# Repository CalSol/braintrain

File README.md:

# braintrain
These are a series of introductory self-paced labs teaching beginning embedded software engineering concepts.

Labs currently available:
- [Lab 1: Embedded Introduction](lab1.md)
- [Lab 2: CAN Bus and Multitasking](lab2.md)

References for non-firmware labs:
- [Soldering](soldering.md)

Coming soon:
- Suggest something!

## Setup
To get started, you need to setup the PlatformIO build system and clone this repository.
Follow the [detailed setup instructions](SETUP.md).

## Troubleshooting
Find the solutions to your troubles here:
- [Troubleshoot.md](Troubleshoot.md)
- [CalSol Wiki on Nucleo](https://www.google.com/) Sorry I forgot the link. You can search it up on the wiki.

## Quick Reference
To upload firmware to the board from the command line, run:
```
pio run -t upload
```

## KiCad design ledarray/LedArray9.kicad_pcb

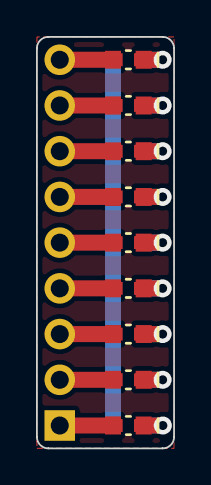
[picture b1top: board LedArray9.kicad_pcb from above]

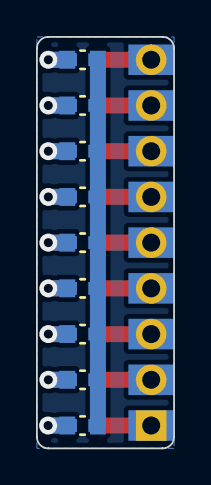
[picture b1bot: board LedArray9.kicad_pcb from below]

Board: 2 copper layers, 7.6 x 22.9 mm, 19 parts (10 on the bottom side), 19 nets.

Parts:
D1, D2, D3, D4, D5, D6, D7, D8, D9: D; LED_0603_0402_combo
J1: Conn_01x09; Pin_Header_Inline_1x09_Pitch2.54mm
R1, R2, R3, R4, R5, R6, R7, R8, R9: R; R_0603_0402_combo

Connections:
unnamed: D1.1, R1.2
unnamed: D1.2, J1.1
unnamed: D2.1, R2.2
unnamed: D2.2, J1.2
unnamed: D3.1, R3.2
unnamed: D3.2, J1.3
unnamed: D4.1, R4.2
unnamed: D4.2, J1.4
unnamed: D5.1, R5.2
unnamed: D5.2, J1.5
unnamed: D6.1, R6.2
unnamed: D6.2, J1.6
unnamed: D7.1, R7.2
unnamed: D7.2, J1.7
unnamed: D8.1, R8.2
unnamed: D8.2, J1.8
unnamed: D9.1, R9.2
unnamed: D9.2, J1.9
unnamed: R1.1, R2.1, R3.1, R4.1, R5.1, R6.1, R7.1, R8.1, R9.1

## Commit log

2016-11-30 Add submodules
2016-11-30 Import zephyr libraries, initial main
2016-12-23 Refactors to use latest mbed, remove zephyr-common pending further refactoring
2016-12-25 Reduce clock rate to 12MHz using override system files, up default baud to 115200
2016-12-26 Clean skeleton code with broken out utils
2016-12-26 Use stdlib abs and fabs, which result in faster runtime
2016-12-26 Default to -O2 optimization
2016-12-28 First two labs
2016-12-28 Lab 1.4 and updates to previous
2016-12-28 fixes
2016-12-28 fix cross-repo links
2016-12-29 Finish lab 1
2016-12-29 try reformatting
2016-12-29 Remove unused code, corrections to lab
2016-12-29 Add braintest binaries and source
2016-12-29 braintest instructions
2016-12-30 diagrams and DONE
2016-12-31 Add debouncing mention
2017-01-05 Auto-build solutions, add openocd build target
2017-01-30 Use upstream mbed
2017-02-21 can intro
2017-02-21 CAN PHY overview
2017-02-21 unreverse links
2017-02-21 lab sketch
2017-02-21 rewording
2017-02-22 Lab 2.2 and partial master node code
2017-02-27 Lab2 master debouncing code
2017-03-06 Updated lab2 master with RGB LED and CAN spam
2017-03-06 refactor RGB LED
2017-03-06 fix RGB LED code
2017-03-06 Rest of lab2
2017-03-06 cooperative multitasking
2017-03-06 add rtos to build
2017-03-08 RTOS lab 2.6
2017-03-08 RTOS lab
2017-03-09 rewrite threading discussion
2017-03-10 Build the USBDevice library
2017-03-10 Add SLCAN debug interface
    Add quasi-standard CAN-USB/SLCAN protocol CAN debug support
    See lab2slcan for example usage
2017-03-10 Change lab2slcan to use native USB
2017-03-10 Add BufferedRXSerial class
    Add interrupt-based buffered RX serial class
    Add utility library to the build (for solutions only)
2017-03-10 Add USBSLCANSlave for SLCAN over native USB
    Refactor command buffering into SLCANBase::readCommand()
    Split SerialSLCAN details into its own header and implementation file
    Add USBSLCAN implementation
2017-03-10 Move lab2slcan to util/
2017-03-11 Silently ignore empty commands
2017-03-11 Fix responses to diagnostic commands over USB
2017-03-11 Remove the hardware serial SLCAN implementation
    Removed the SerialSLCANBase/SerialSLCANMaster/Slave classes
    Removed BufferedSerial, as it no longer has a purpose
    Changed SLCANBase::readCommand() to use wrapper methods in subclasses
    instead of directly calling stream.readable() and stream.getc() to avoid
    interface splitting issues
2017-03-11 Only echo CAN messages sent by the node, not the host
2017-03-11 Fix hang when disconnecting USB
    Add NonBlockingUSBSerial class to expose the nonblocking USB EP write
    API via writeBlockNB
    Change the activity flag to only be used for reporting activity.
    Always attempt to flush the SLCAN USB output buffer to avoid stalling on
    a full packet buffer
2017-03-11 Reset output buffers after a USB disconnect
2017-03-11 fixup! Fix hang when disconnecting USB
2017-03-11 Change command responses to return fixed lengths
    execCommand no longer nul-terminates response strings - the result is
    either the length returned by commandResponseLength() on success or 1 on
    failure
    Pass the command response directly into the output packet buffer
2017-03-11 Move USBDevice build into SConscript-env-lpc1549
2017-03-12 Add CAN->USB debugging using the SLCAN protocol
    This commit adds a lab2slcan variant of the lab2master node firmware that reports CAN messages over USB using the CAN-USB/SLCAN[1] protocol.
    The lab2slcan firmware and supporting files can be found under the util/ directory.
    Some CAN-USB commands have not been fully implemented. For compatibility, several commands are accepted, but have no effect. In particular, the lab2slcan firmware will not allow the host PC to change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
    The lab2slcan firmware has been tested for compatibility with USBtinViewer[2] and the UAVCAN GUI Tool[3].
    1: http://www.can232.c
2017-03-12 fix some code, use non-RTR frames
2017-03-12 Lab 2 updates
2017-03-12 Master SLCAN transmit loopback
2017-03-12 caveat
2017-03-12 better index
2017-03-13 add voltage instruction
2017-03-24 Add notes on zephyr-common stuff
2018-09-18 Fix gitmodules to use HTTPS
2018-10-05 Update build system with Tachyon-FW system
2018-10-05 refactor out libs to be more independent of mbed
2018-10-05 improved docs
2018-10-05 no more zephyr races
2018-10-05 remove some legacy stuff
2018-10-16 Update build system and readme (#4)
    Update build system with Tachyon-FW system
2019-02-15 rami doing the brain training and practicing git; do not use
2019-09-07 Adding Mac serial instructions, need pics
2019-09-08 my old braintrain solution
2019-09-08 2019 CAN Controller Blinky, change pin outs for each brain
2019-09-09 minor changes to lab text
2019-09-15 Clarify parts of the RGB led section
2019-09-15 Header instructions
2019-09-19 Added brain pinout diagram
2019-10-21 Clarify how to clone
2019-10-21 Lab 5
2020-03-05 Adding last changes to main
2020-10-12 add stm32f303k8 build support alongside lpc1549
2020-10-12 revert brain dirs for doc compatibility
2020-10-13 Fix RTOS platform target
2020-10-13 add hue blinky for stm32
2020-10-19 Nucleo F303K8 build (#6)
    * add stm32f303k8 build support alongside lpc1549
    * revert brain dirs for doc compatibility
    * Fix RTOS platform target
    * add hue blinky for stm32
2021-09-11 purge
2021-09-11 purge 2
2021-09-11 basic build config wip
2021-09-11 kinda doing ... not much actually =(
2021-09-11 working!
2021-09-11 apparent wait has ms resolution...
2021-09-11 update docs
2021-09-11 add pictures
2021-09-15 updated mbed to 5.15.6
2021-09-15 updated labs
2021-09-15 updated platformio.ini
2021-09-18 breadboard and standard parts
2021-09-18 all done (ish)
2021-09-18 more pictures
2021-09-21 swap code to f042k6
2021-09-21 swapped lab doc to f042k6
2021-09-21 minor shuffling
2021-09-21 added sanity check
2021-09-21 changed sanity code to rgb fade
2021-09-21 update wording
2021-09-21 Update labs to use NUCLEO-F303K8 (#8)
2021-09-21 save code space ,refactor naming, downclock
2021-09-21 solutions at 2400Hz LED update, serial monitor instructions
2021-09-21 cleanup
2021-09-27 convert to f042k6
2021-09-28 added can reset fix, WIP slcan port
2021-09-28 updated docs
2021-09-28 can diagrams
2021-09-28 include diagrams intext
2021-09-28 soldering training board + renders
2021-09-28 soldering reference doc
2024-03-02 added nucleo mbed not support fix
